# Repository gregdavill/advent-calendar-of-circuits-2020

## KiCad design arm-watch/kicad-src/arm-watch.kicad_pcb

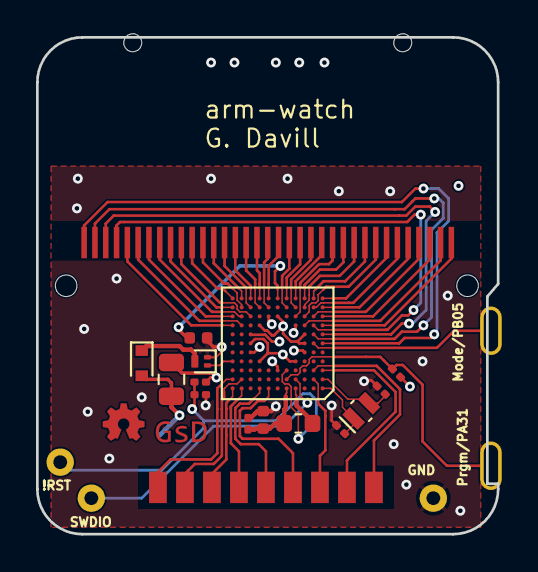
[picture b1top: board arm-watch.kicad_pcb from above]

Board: 4 copper layers, 25.6 x 27.6 mm, 17 parts (0 on the bottom side), 58 nets.

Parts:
BRD1: CA53BOARD; ca53board
C1, C2: 8pF; C_0201_0603Metric
C3, C4: 0.1uF; C_0201_0603Metric
C5: 4.7uF; C_0402_1005Metric
C6: 4.7uF; R_0402_1005Metric
D1: D_Schottky_ALT; D_SOD-523
KPD1: CA53KEYPAD; ca53keypad
L1: 10uH; L_0603_1608Metric
L2: 10uH; L_0805_2012Metric
LCD1: CA53LCD; ca53lcd
Q1: Q_NMOS_GSD; SOT-883
R1: 1k; R_0201_0603Metric
R2: 10K; R_0201_0603Metric
U1: ATSAML22N16A-CFUT; BGA-100_6.0x6.0mm_Layout11x11_P0.5mm_Ball0.3mm_Pad0.25mm_NS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
Y1: 32.768KHz; Crystal_SMD_MicroCrystal_CM9V-T1A-2Pin_1.6x1.0mm

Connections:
+3V0: BRD1.1 (VCC), L2.1, R1.1, R2.1, U1.D4 (VDDIO[5]), U1.D8 (VDDIO[5]), U1.F3 (VDDANA[2]), U1.F9 (VDDIO[5]), U1.G3 (VDDANA[2]), U1.H8 (VDDIO[5]), U1.J6 (VDDIO[5])
/BUZZER: Q1.1 (G), U1.D11 (PB20/EIC[4]/LP[46]/SC3[0]/SC5[0])
/KEY0: KPD1.1, U1.B11 (PA22/EIC[6]/LP[50]/SC0[2]/SC2[0])
/KEY1: KPD1.2, U1.B10 (PA23/EIC[7]/LP[51]/SC0[3]/SC2[1])
/KEY2: KPD1.3, U1.A11 (PA24/EIC[12]/SC2[2]/SC5[0])
/KEY3: KPD1.4, U1.A10 (PA25/EIC[13]/SC2[3]/SC5[1])
/KEY4: KPD1.5, U1.A8 (PB23/EIC[7]/SC0[3]/SC5[3])
/KEY5: KPD1.6, U1.A7 (PC27/EIC[3]/SC1[0])
/KEY6: KPD1.7, U1.B2 (PB01/EIC[1]/SC3[3]/SC5[3])
/KEY7: KPD1.8, U1.C1 (PC02/EIC[10])
/KEY8: KPD1.9, U1.C2 (PC01/EIC[9])
/LCD_COM0: LCD1.1 (COM0), U1.F1 (PB06/EIC[6]/LP[0])
/LCD_COM1: LCD1.2 (COM1), U1.G2 (PB07/EIC[7]/LP[1])
/LCD_COM2: LCD1.3 (COM2), U1.G1 (PB08/EIC[8]/LP[2]/SC3[0])
/LCD_COM3: LCD1.4 (COM3), U1.H2 (PB09/EIC[9]/LP[3]/SC3[1])
/LCD_SEG0: LCD1.5 (SEG01), U1.H11 (PC18/EIC[10]/LP[38])
/LCD_SEG1: LCD1.6 (SEG02), U1.H10 (PC17/EIC[9]/LP[37])
/LCD_SEG2: LCD1.7 (SEG03), U1.J11 (PC16/EIC[8]/LP[36])
/LCD_SEG3: LCD1.8 (SEG04), U1.J10 (PA19/EIC[3]/LP[35]/SC1[3]/SC2[3])
/LCD_SEG4: LCD1.9 (SEG04), U1.K11 (PA17/EIC[1]/LP[33]/SC1[1]/SC2[1])
/LCD_SEG5: LCD1.10 (SEG05), U1.J9 (PA16/EIC[0]/LP[32]/SC1[0]/SC2[0])
/LCD_SEG6: LCD1.11 (SEG06), U1.L11 (PA15/EIC[15]/LP[31]/SC4[3]/SC3[3])
/LCD_SEG7: LCD1.12 (SEG07), U1.K10 (PA14/EIC[14]/LP[30]/SC4[2]/SC3[2])
/LCD_SEG8: LCD1.13 (SEG08), U1.L10 (PA13/EIC[13]/LP[29]/SC4[1]/SC3[1])
/LCD_SEG9: LCD1.14 (SEG09), U1.K9 (PA12/EIC[12]/LP[28]/SC4[0]/SC3[0])
/LCD_SEG10: LCD1.15 (SEG10), U1.L9 (PC15/EIC[7]/LP[27])
/LCD_SEG11: LCD1.16 (SEG11), U1.K8 (PB14/EIC[14]/LP[24]/SC3[2])
/LCD_SEG12: LCD1.17 (SEG12), U1.L8 (PB15/EIC[15]/LP[25]/SC3[3])
/LCD_SEG13: LCD1.18 (SEG13), U1.K7 (PB12/EIC[12]/LP[22]/SC3[0])
/LCD_SEG14: LCD1.19 (SEG14), U1.L7 (PB13/EIC[13]/LP[23]/SC3[1])
/LCD_SEG15: LCD1.20 (SEG15), U1.K5 (PC12/EIC[4]/LP[19]/SC1[0])
/LCD_SEG16: LCD1.21 (SEG16), U1.L5 (PC13/EIC[5]/LP[20]/SC1[1])
/LCD_SEG17: LCD1.22 (SEG17), U1.K4 (PC10/EIC[2]/LP[17]/SC1[2])
/LCD_SEG18: LCD1.23 (SEG18), U1.L4 (PC11/EIC[3]/LP[18]/SC1[3])
/LCD_SEG19: LCD1.24 (SEG19), U1.J4 (PA10/EIC[10]/LP[13]/SC0[2]/SC4[2])
/LCD_SEG20: LCD1.25 (SEG20), U1.L3 (PC08/EIC[0]/LP[15])
/LCD_SEG21: LCD1.26 (SEG21), U1.K3 (PA11/EIC[11]/LP[14]/SC0[3]/SC4[3])
/LCD_SEG22: LCD1.27 (SEG22), U1.L2 (PA09/EIC[9]/LP[12]/SC0[1]/SC4[1])
/LCD_SEG23: LCD1.28 (SEG23), U1.J3 (PC07/EIC[15]/LP[10])
/LCD_SEG24: LCD1.29 (SEG24), U1.L1 (PA08/NMI/LP[11]/SC0[0]/SC4[0])
/LCD_SEG25: LCD1.30 (SEG25), U1.K2 (PC06/EIC[14]/LP[9])
/LCD_SEG26: LCD1.31 (SEG26), U1.K1 (PC05/EIC[13]/LP[8])
/LCD_SEG27: LCD1.32 (SEG27), U1.J2 (PA07/EIC[7]/LP[7]/SC0[3])
/LCD_SEG28: LCD1.33 (SEG28), U1.J1 (PA06/EIC[6]/LP[6]/SC0[2])
/LCD_SEG29: LCD1.34 (SEG29), U1.H3 (PA05/EIC[5]/LP[5]/SC0[1])
/LCD_SEG30: LCD1.35 (SEG30), U1.H1 (PA04/EIC[4]/LP[4]/SC0[0])
/MODE: BRD1.3 (MODE), U1.F2 (PB05/EIC[5])
/RST_N: BRD1.6 (!RST), C4.1, R2.2, U1.C5 (RESET_N)
/SWCLK: BRD1.4 (PRGM), R1.2, U1.B5 (PA30/EIC[10]/SC1[2]/SWCLK)
/SWDIO: BRD1.5 (TST), U1.B4 (PA31/EIC[11]/SC1[3]/SWDIO)
GND: BRD1.2 (GND), BRD1.7 (GND), C1.2, C2.2, C3.2, C4.2, C5.2, C6.2, Q1.2 (S), U1.C6 (GNDIO[5]), U1.E3 (GNDANA[2]), U1.E9 (GNDIO[5]), U1.G9 (GNDIO[5]), U1.H4 (GNDANA[2]), U1.J7 (GNDIO[5])
unnamed: BRD1.8 (BUZZ), D1.2 (A), L2.2
unnamed: C1.1, U1.B1 (PA01/EIC[1]/SC1[1]), Y1.2
unnamed: C2.1, U1.A1 (PA00/EIC[0]/SC1[0]), Y1.1
unnamed: C3.1, C5.1, L1.2, U1.A5 (VDDCORE)
unnamed: D1.1 (K), Q1.3 (D)
unnamed: L1.1, U1.A4 (VSW)
unnamed: C6.1, U1.L6 (VLCD)

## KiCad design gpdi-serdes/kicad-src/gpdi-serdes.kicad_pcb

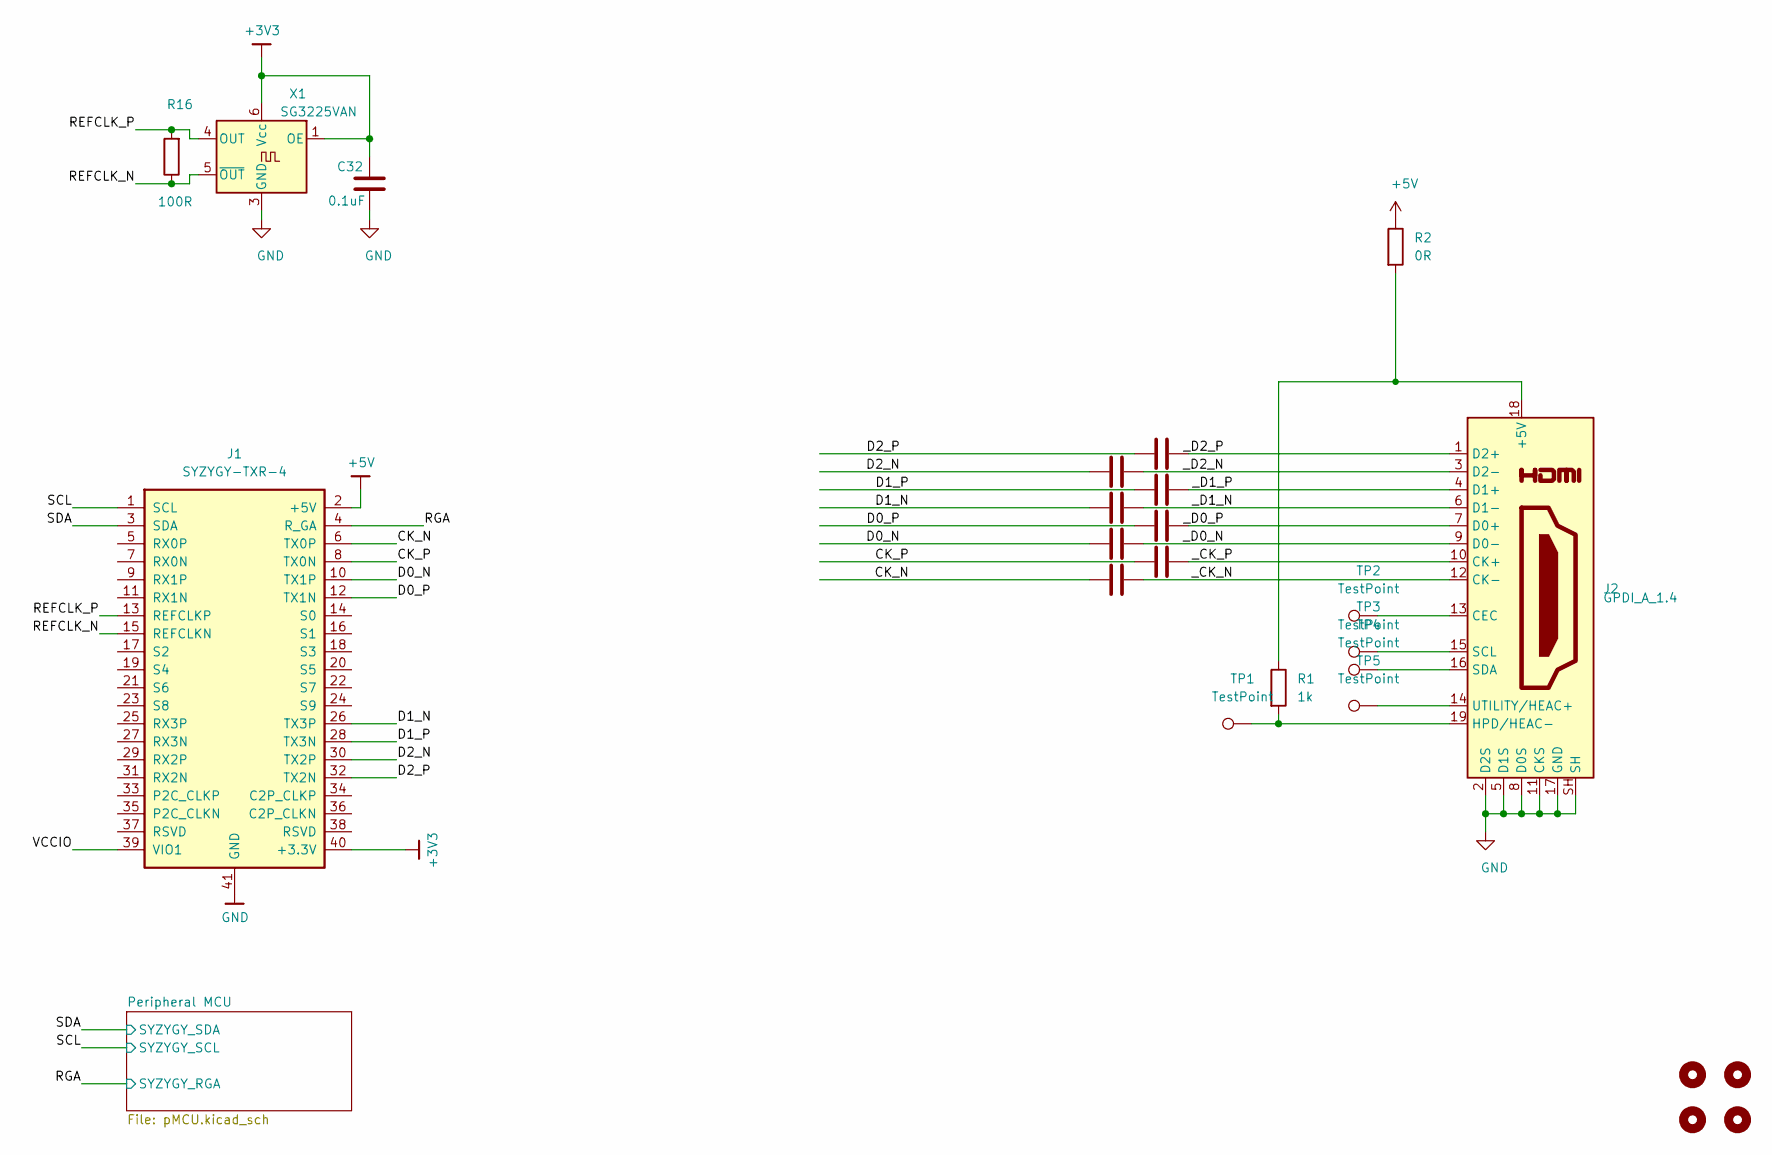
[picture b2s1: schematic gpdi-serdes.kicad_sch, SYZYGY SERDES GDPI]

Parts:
C1, C2, C3, C4, C5, C6, C7, C8: 0.1u; C_0402_1005Metric
C32: 0.1uF; C_0402_1005Metric
H1, H2, H3, H4: MountingHole; MountingHole_3.2mm_M3
J1: SYZYGY-TXR-4; SYZYGY-TXR-POD
J2: GPDI_A_1.4; HDMI-10029449-111RLF
R1: 1k; R_0402_1005Metric
R2: 0R; R_0402_1005Metric
R16: 100R; R_0402_1005Metric
TP1, TP2, TP3, TP4, TP5: TestPoint; TestPoint_THTPad_D1.5mm_Drill0.7mm
X1: SG3225VAN; Oscillator_SMD_Silicon_Labs_LGA-6_2.5x3.2mm_P1.25mm

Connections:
+3V3: C32.1, J1.40 (+3.3V), X1.1 (OE), X1.6 (Vcc); also elsewhere on the board
+5V: J1.2 (+5V), R2.1
/CK_N: C4.1, J1.6 (TX0P)
/CK_P: C8.1, J1.8 (TX0N)
/D0_N: C3.1, J1.10 (TX1P)
/D0_P: C7.1, J1.12 (TX1N)
/D1_N: C2.1, J1.26 (TX3P)
/D1_P: C6.1, J1.28 (TX3N)
/D2_N: C1.1, J1.30 (TX2P)
/D2_P: C5.1, J1.32 (TX2N)
/REFCLK_N: J1.15 (REFCLKN), R16.1, X1.5 (~OUT)
/REFCLK_P: J1.13 (REFCLKP), R16.2, X1.4 (OUT)
/RGA: J1.4 (R_GA); also elsewhere on the board
/SCL: J1.1 (SCL); also elsewhere on the board
/SDA: J1.3 (SDA); also elsewhere on the board
/VCCIO: J1.39 (VIO1)
/_CK_N: C4.2, J2.12 (CK-)
/_CK_P: C8.2, J2.10 (CK+)
/_D0_N: C3.2, J2.9 (D0-)
/_D0_P: C7.2, J2.7 (D0+)
/_D1_N: C2.2, J2.6 (D1-)
/_D1_P: C6.2, J2.4 (D1+)
/_D2_N: C1.2, J2.3 (D2-)
/_D2_P: C5.2, J2.1 (D2+)
GND: C32.2, J1.41 (GND), J2.2 (D2S), J2.5 (D1S), J2.8 (D0S), J2.11 (CKS), J2.17 (GND), J2.SH, X1.3 (GND); also elsewhere on the board
unnamed: J2.13 (CEC), TP2.1
unnamed: J2.14 (UTILITY/HEAC+), TP5.1
unnamed: J2.15 (SCL), TP3.1
unnamed: J2.16 (SDA), TP4.1
unnamed: J2.18 (+5V), R1.1, R2.2
unnamed: J2.19 (HPD/HEAC-), R1.2, TP1.1

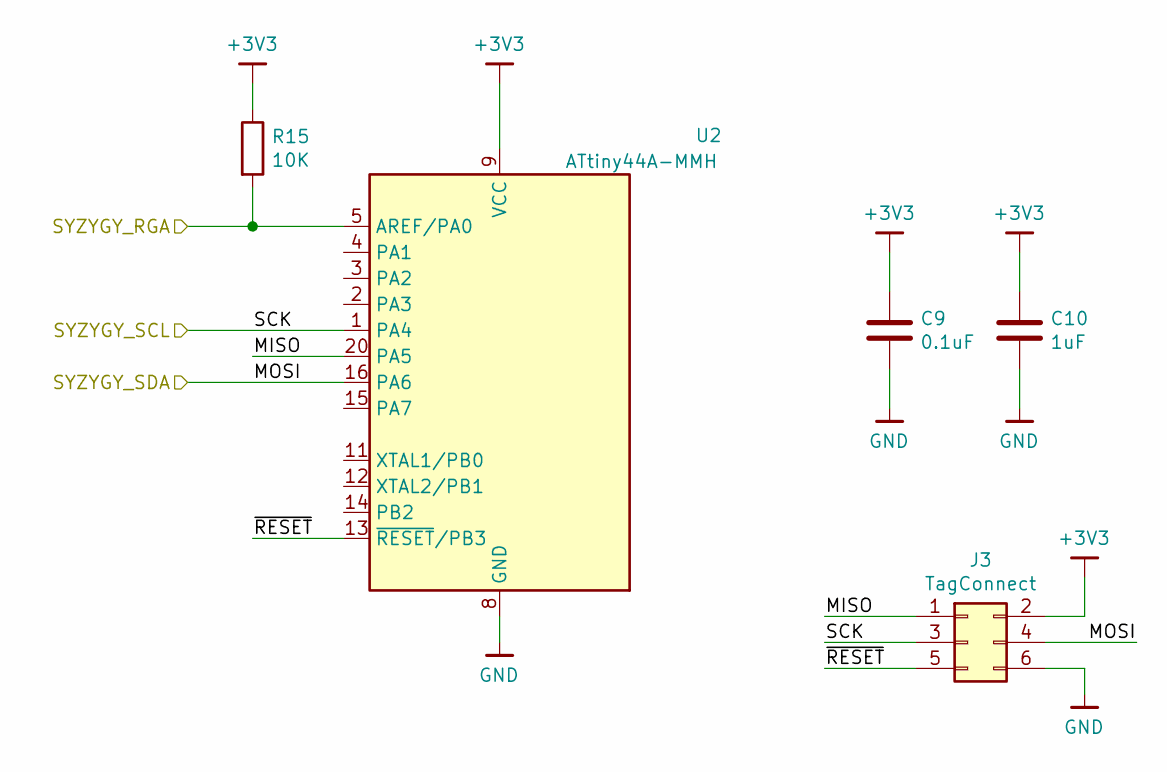
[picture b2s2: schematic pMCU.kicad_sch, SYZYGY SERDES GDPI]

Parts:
C9: 0.1uF; C_0402_1005Metric
C10: 1uF; C_0402_1005Metric
J3: TagConnect; TC2030-NL_SMALL
R15: 10K; R_0402_1005Metric
U2: ATtiny44A-MMH; QFN-20-1EP_3x3mm_P0.45mm_EP1.6x1.6mm

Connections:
+3V3: C9.1, C10.1, J3.2, R15.1, U2.9 (VCC); also elsewhere on the board
/Peripheral MCU/MISO: J3.1, U2.20 (PA5)
/Peripheral MCU/~RESET: J3.5, U2.13 (~RESET~/PB3)
/RGA: R15.2, U2.5 (AREF/PA0); also elsewhere on the board
/SCL: J3.3, U2.1 (PA4); also elsewhere on the board
/SDA: J3.4, U2.16 (PA6); also elsewhere on the board
GND: C9.2, C10.2, J3.6, U2.8 (GND), U2.21 (GND); also elsewhere on the board
no_connect_65: U2.10 (NC)
no_connect_66: U2.17 (NC)
no_connect_67: U2.18 (NC)
no_connect_68: U2.19 (NC)
no_connect_69: U2.6 (NC)
no_connect_70: U2.7 (NC)

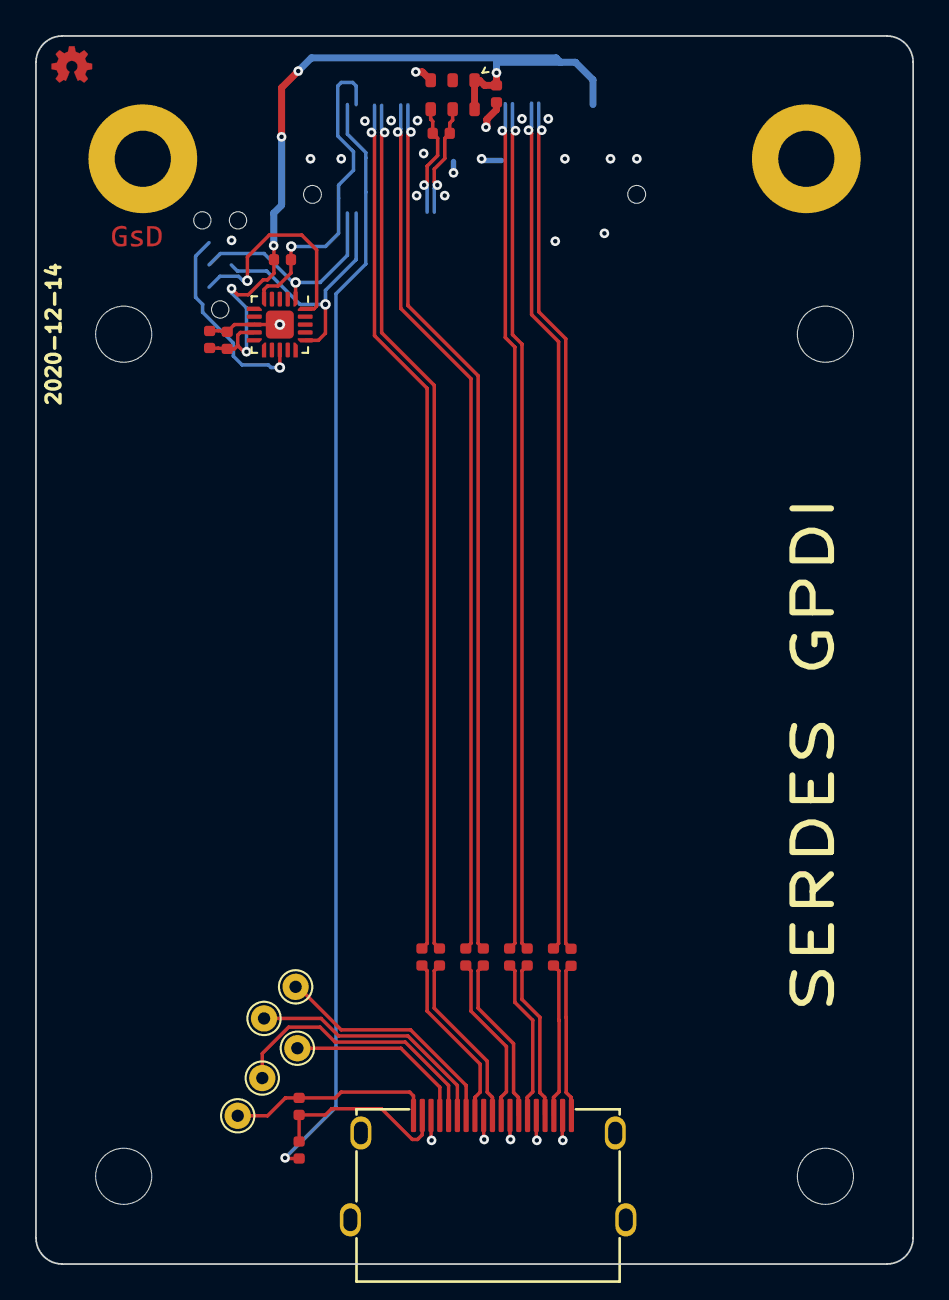
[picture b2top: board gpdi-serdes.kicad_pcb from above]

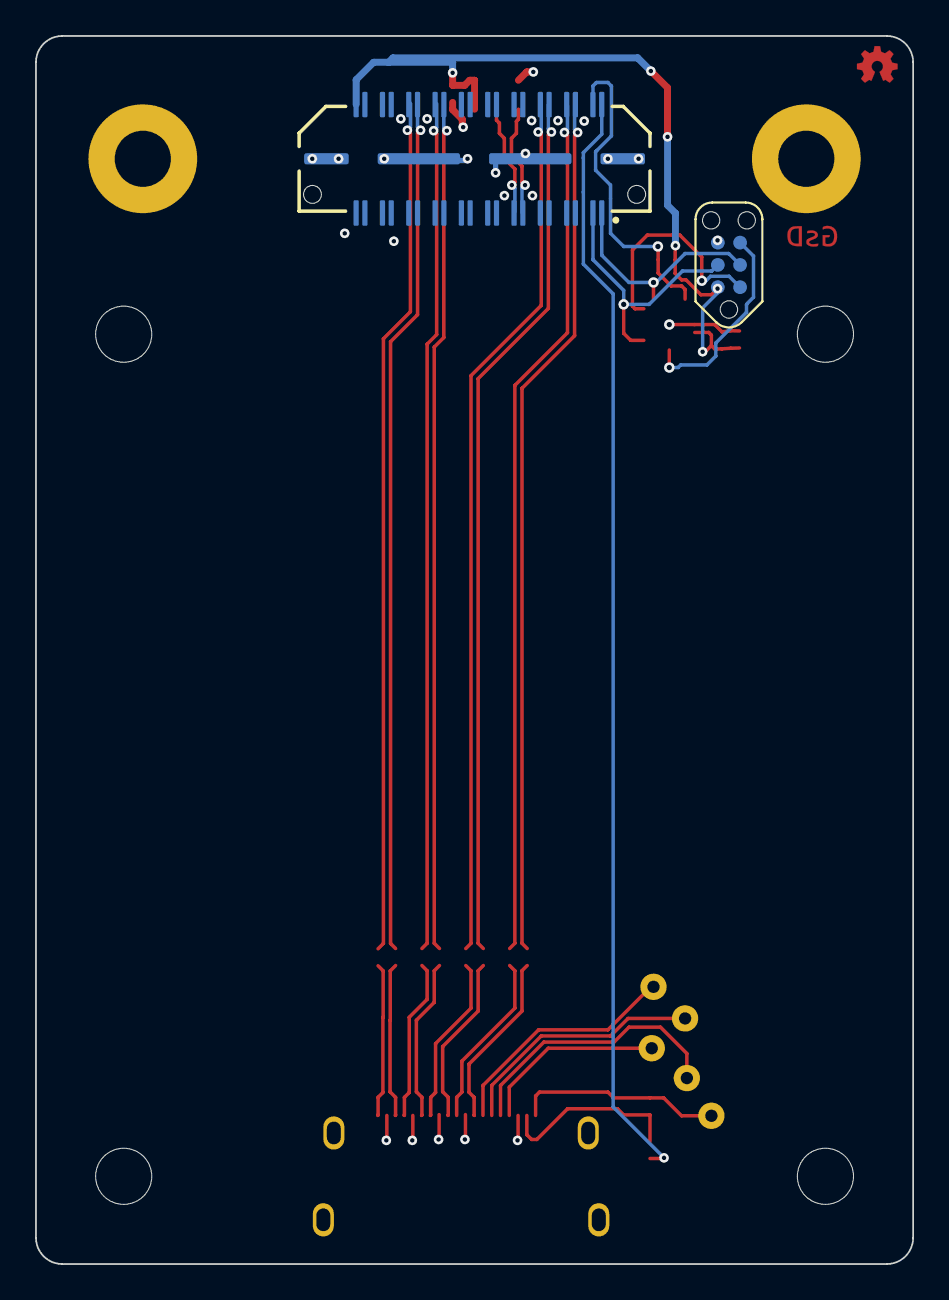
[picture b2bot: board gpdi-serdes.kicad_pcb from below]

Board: 4 copper layers, 50.0 x 70.0 mm, 29 parts (2 on the bottom side), 32 nets.

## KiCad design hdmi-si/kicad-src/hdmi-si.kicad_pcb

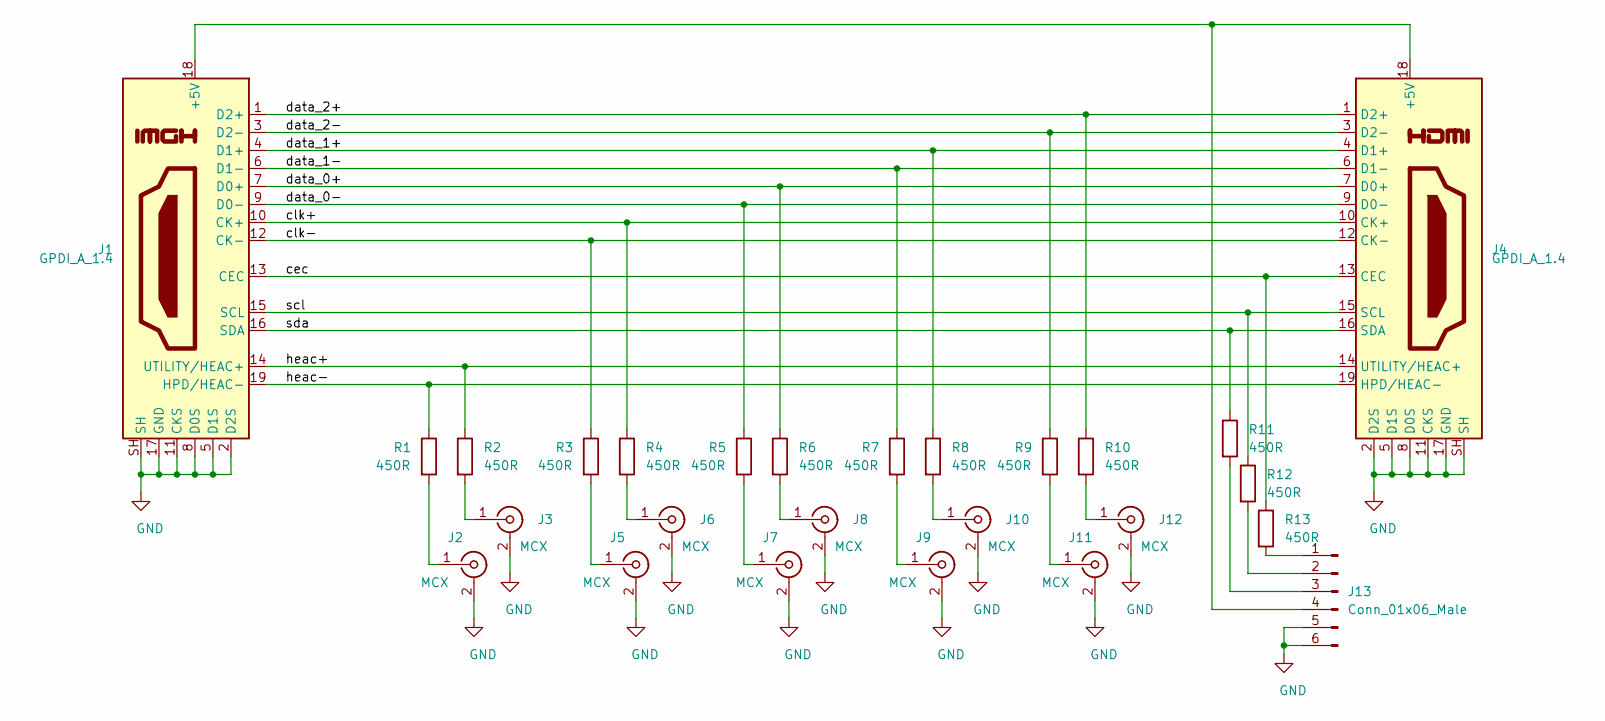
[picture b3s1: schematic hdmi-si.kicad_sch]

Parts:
J1, J4: GPDI_A_1.4; HDMI-10029449-111RLF
J2, J3, J5, J6, J7, J8, J9, J10, J11, J12: MCX; MMCX_Molex_73415-1471_Vertical
J13: Conn_01x06_Male; PinHeader_1x06_P2.54mm_Vertical
R1, R2, R3, R4, R5, R6, R7, R8, R9, R10, R11, R12, R13: 450R; R_0402_1005Metric

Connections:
/cec: J1.13 (CEC), J4.13 (CEC), R13.1
/clk+: J1.10 (CK+), J4.10 (CK+), R4.1
/clk-: J1.12 (CK-), J4.12 (CK-), R3.1
/data_0+: J1.7 (D0+), J4.7 (D0+), R6.1
/data_0-: J1.9 (D0-), J4.9 (D0-), R5.1
/data_1+: J1.4 (D1+), J4.4 (D1+), R8.1
/data_1-: J1.6 (D1-), J4.6 (D1-), R7.1
/data_2+: J1.1 (D2+), J4.1 (D2+), R10.1
/data_2-: J1.3 (D2-), J4.3 (D2-), R9.1
/heac+: J1.14 (UTILITY/HEAC+), J4.14 (UTILITY/HEAC+), R2.1
/heac-: J1.19 (HPD/HEAC-), J4.19 (HPD/HEAC-), R1.1
/scl: J1.15 (SCL), J4.15 (SCL), R12.1
/sda: J1.16 (SDA), J4.16 (SDA), R11.1
GND: J1.2 (D2S), J1.5 (D1S), J1.8 (D0S), J1.11 (CKS), J1.17 (GND), J1.SH, J2.2 (Ext), J3.2 (Ext), J4.2 (D2S), J4.5 (D1S), J4.8 (D0S), J4.11 (CKS), J4.17 (GND), J4.SH, J5.2 (Ext), J6.2 (Ext), J7.2 (Ext), J8.2 (Ext), J9.2 (Ext), J10.2 (Ext), J11.2 (Ext), J12.2 (Ext), J13.5, J13.6
unnamed: J1.18 (+5V), J4.18 (+5V), J13.4
unnamed: J2.1 (In), R1.2
unnamed: J3.1 (In), R2.2
unnamed: J5.1 (In), R3.2
unnamed: J6.1 (In), R4.2
unnamed: J7.1 (In), R5.2
unnamed: J8.1 (In), R6.2
unnamed: J9.1 (In), R7.2
unnamed: J10.1 (In), R8.2
unnamed: J11.1 (In), R9.2
unnamed: J12.1 (In), R10.2
unnamed: J13.1, R13.2
unnamed: J13.2, R12.2
unnamed: J13.3, R11.2

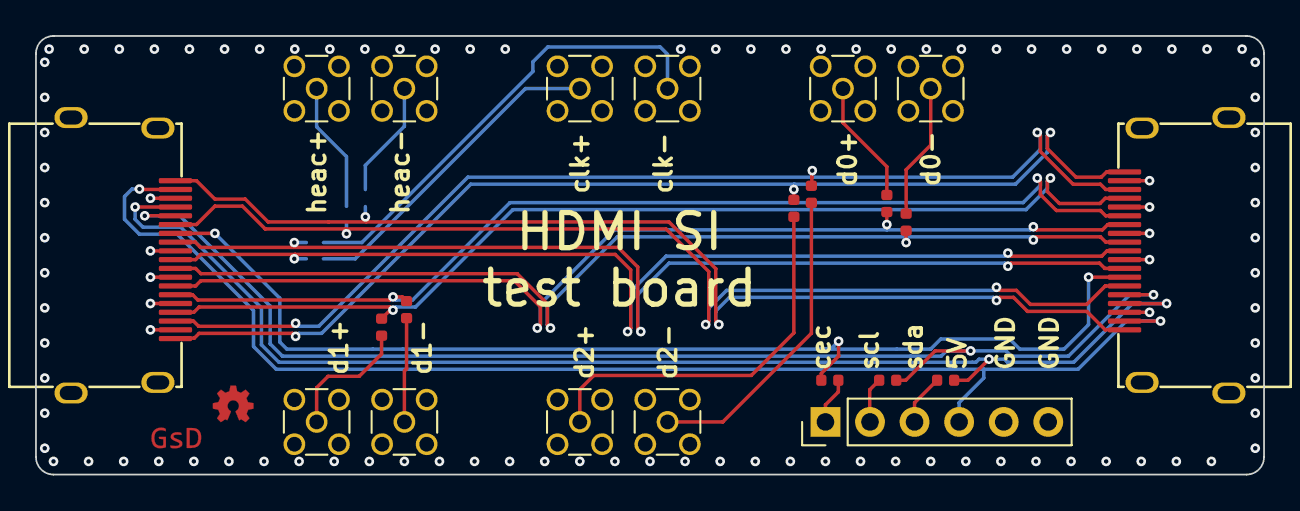
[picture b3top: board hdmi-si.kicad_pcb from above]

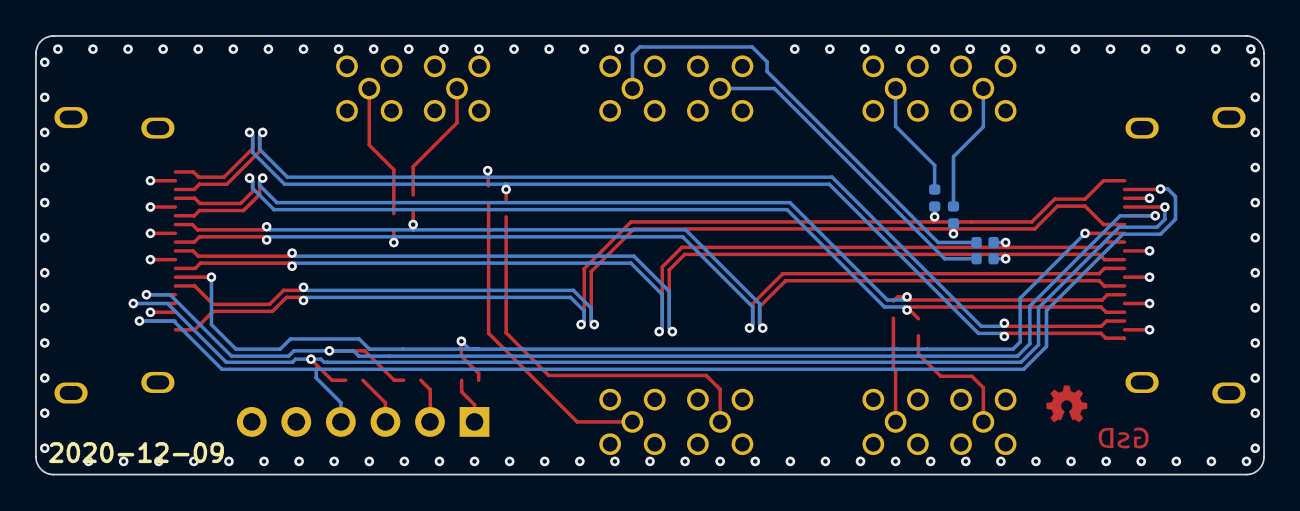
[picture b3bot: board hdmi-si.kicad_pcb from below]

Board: 4 copper layers, 70.0 x 25.0 mm, 26 parts (4 on the bottom side), 28 nets.

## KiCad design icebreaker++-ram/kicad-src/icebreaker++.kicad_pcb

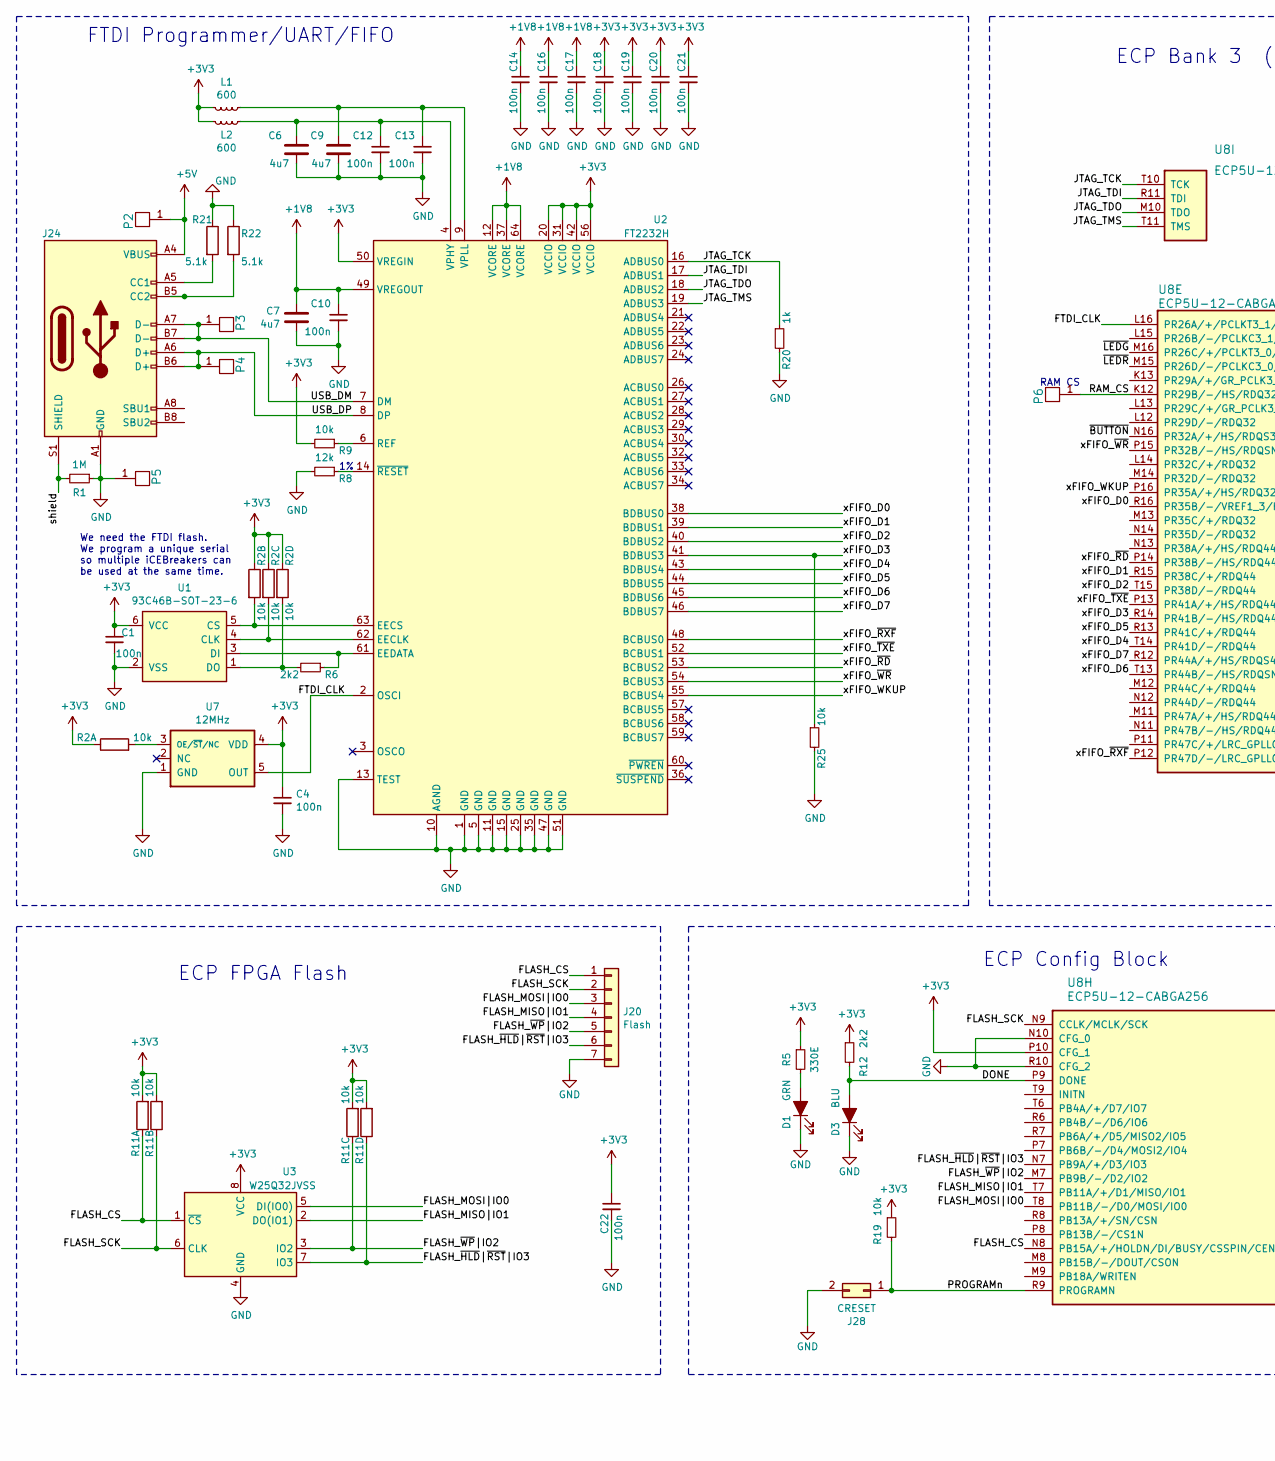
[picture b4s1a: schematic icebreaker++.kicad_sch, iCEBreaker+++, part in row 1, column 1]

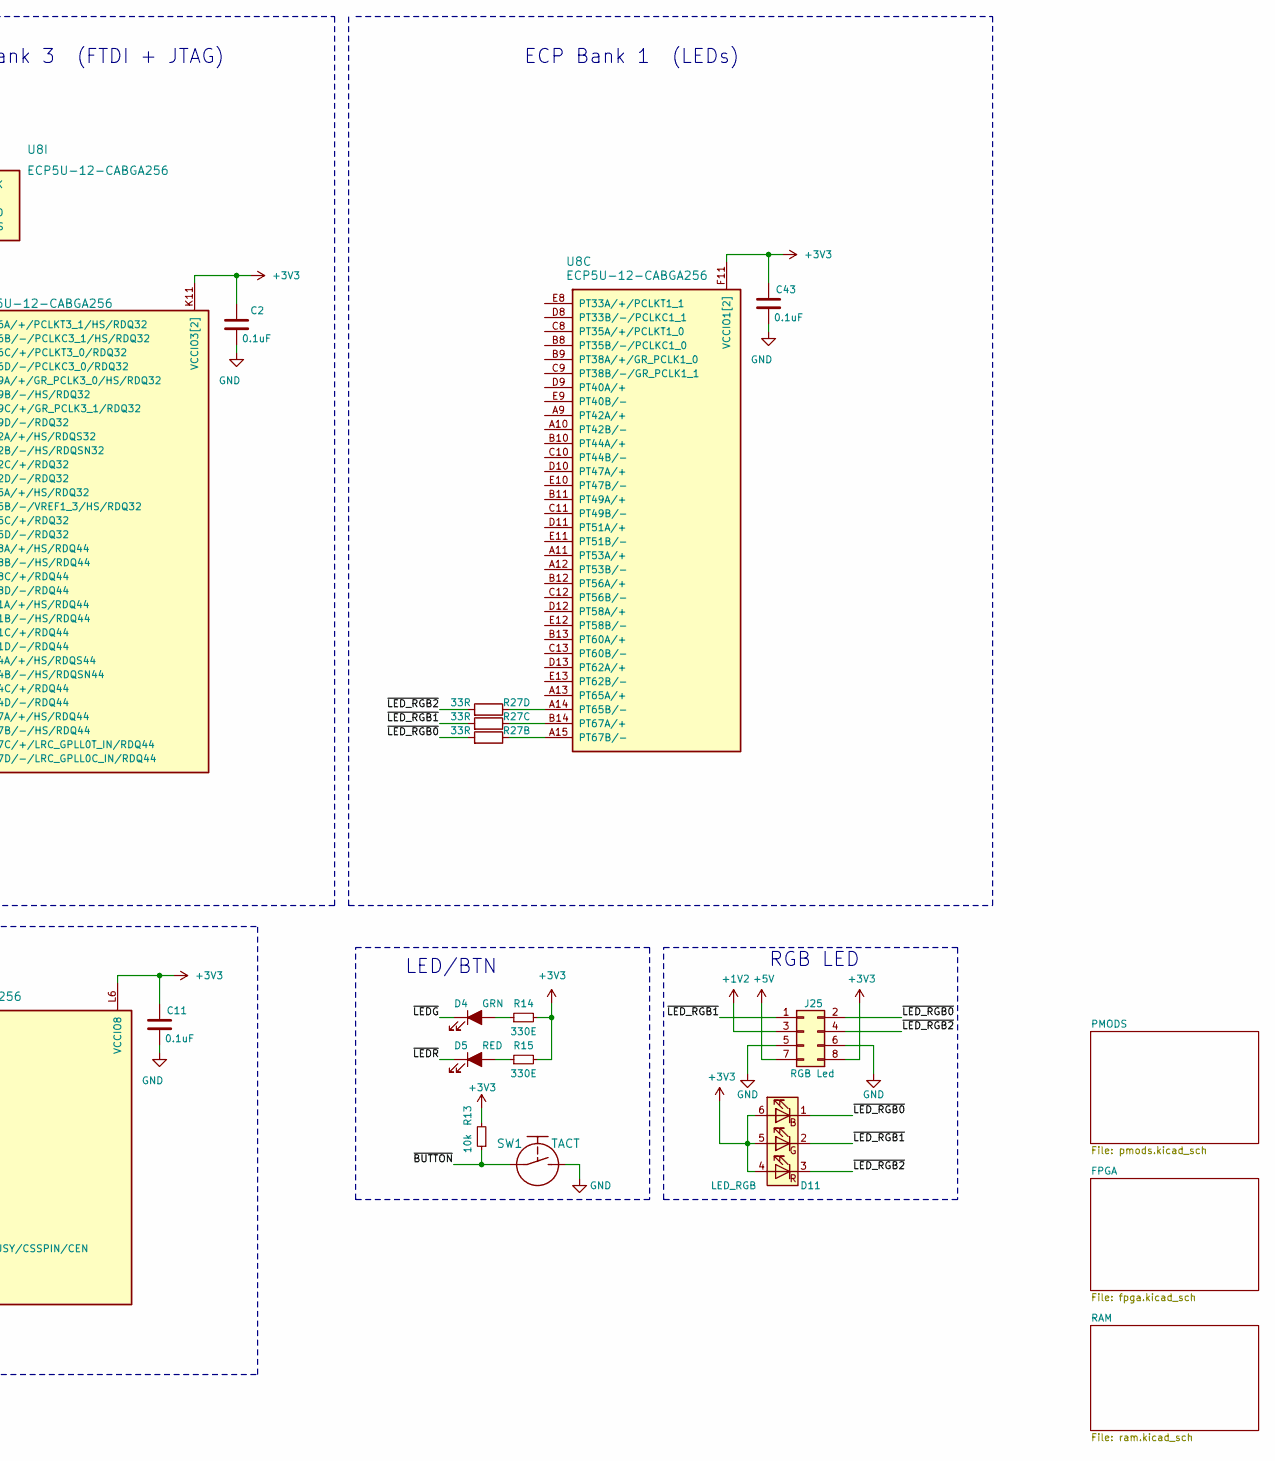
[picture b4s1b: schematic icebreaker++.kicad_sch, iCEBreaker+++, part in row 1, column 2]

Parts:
C1, C4, C10, C12, C13, C14, C16, C17, C18, C19, C20, C21, C22: 100n; C_0402_1005Metric
C2, C11, C43: 0.1uF; C_0402_1005Metric
C6, C7, C9: 4u7; C_0603_1608Metric
D1, D4: GRN; LED_0603_1608Metric
D3: BLU; LED_0603_1608Metric
D5: RED; LED_0603_1608Metric
D11: LED_RGB; LED_Cree_PLCC6_3.4x3.4mm
J20: Flash; PinHeader_1x07_P2.54mm_Vertical
J24: USB_C_Receptacle_USB2.0; USB_C_Receptacle_HRO_TYPE-C-31-M-12
J25: RGB Led; PinHeader_2x04_P2.54mm_Vertical
J28: CRESET; PinHeader_2x01_P2.54mm_Vertical
L1, L2: 600; L_0402_1005Metric
P2, P3, P4, P5: UP; PAD_SMD_1x2.65
P6: RAM_CS; PAD_SMD_1x1.5
R1: 1M; R_0402_1005Metric
R2, R11: 10k; R_Array_Convex_4x0402
R5, R14, R15: 330E; R_0402_1005Metric
R6, R12: 2k2; R_0402_1005Metric
R8: 12k; R_0402_1005Metric
R9, R13, R19, R25: 10k; R_0402_1005Metric
R20: 1k; R_0402_1005Metric
R21, R22: 5.1k; R_0402_1005Metric
R27: 33R; R_Array_Convex_4x0402
SW1: TACT; SW_SPST_PTS810
U1: 93C46B-SOT-23-6; SOT-23-6
U2: FT2232H; QFN-64-1EP_9x9mm_P0.5mm_EP4.35x4.35mm
U3: W25Q32JVSS; SOIC-8_5.23x5.23mm_P1.27mm
U7: 12MHz; SOT-23-5
U8: ECP5U-12-CABGA256; BGA-256_14.0x14.0mm_Layout16x16_P0.8mm_Ball0.45mm_Pad0.32mm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

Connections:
+1V2: J25.3
+1V8: C7.1, C10.1, C14.1, C16.1, C17.1, U2.12 (VCORE), U2.37 (VCORE), U2.49 (VREGOUT), U2.64 (VCORE); also elsewhere on the board
+3V3: C1.1, C2.1, C4.1, C11.1, C18.1, C19.1, C20.1, C21.1, C22.1, C43.1, D11.4 (BA), D11.5 (GA), D11.6 (RA), J25.8, L1.1, L2.1, R2.5, R2.6, R2.7, R2.8, R5.1, R9.2, R11.1, R11.2, R11.3, R11.4, R12.1, R13.2, R14.2, R15.2, R19.1, U1.6 (VCC), U2.20 (VCCIO), U2.31 (VCCIO), U2.42 (VCCIO), U2.50 (VREGIN), U2.56 (VCCIO), U3.8 (VCC), U7.4 (VDD), U8.F10 (VCCIO1[2]), U8.F11 (VCCIO1[2]), U8.K11 (VCCIO3[2]), U8.L6 (VCCIO8), U8.L11 (VCCIO3[2]), U8.P10 (CFG_1); also elsewhere on the board
+5V: J24.A4 (VBUS), J24.A9 (VBUS), J24.B4 (VBUS), J24.B9 (VBUS), J25.7, P2.1 (PAD); also elsewhere on the board
/DONE: D3.2 (A), R12.2, U8.P9 (DONE)
/FLASH_CS: J20.1, R11.8, U3.1 (~CS), U8.N8 (PB15A/+/HOLDN/DI/BUSY/CSSPIN/CEN)
/FLASH_MISO|IO1: J20.4, U3.2 (DO(IO1)), U8.T7 (PB11A/+/D1/MISO/IO1)
/FLASH_MOSI|IO0: J20.3, U3.5 (DI(IO0)), U8.T8 (PB11B/-/D0/MOSI/IO0)
/FLASH_SCK: J20.2, R11.7, U3.6 (CLK), U8.N9 (CCLK/MCLK/SCK)
/FLASH_~HLD~|~RST~|IO3: J20.6, R11.5, U3.7 (IO3), U8.N7 (PB9A/+/D3/IO3)
/FLASH_~WP~|IO2: J20.5, R11.6, U3.3 (IO2), U8.M7 (PB9B/-/D2/IO2)
/FTDI_CLK: U2.2 (OSCI), U7.5 (OUT), U8.L16 (PR26A/+/PCLKT3_1/HS/RDQ32)
/JTAG_TCK: R20.1, U2.16 (ADBUS0), U8.T10 (TCK)
/JTAG_TDI: U2.17 (ADBUS1), U8.R11 (TDI)
/JTAG_TDO: U2.18 (ADBUS2), U8.M10 (TDO)
/JTAG_TMS: U2.19 (ADBUS3), U8.T11 (TMS)
/PROGRAMn: J28.1, R19.2, U8.R9 (PROGRAMN)
/RAM_CS: P6.1 (PAD), U8.K12 (PR29B/-/HS/RDQ32)
/USB_DM: J24.A7 (D-), J24.B7 (D-), P3.1 (PAD), U2.7 (DM)
/USB_DP: J24.A6 (D+), J24.B6 (D+), P4.1 (PAD), U2.8 (DP)
/shield: J24.S1 (SHIELD), R1.2
/xFIFO_D0: U2.38 (BDBUS0), U8.R16 (PR35B/-/VREF1_3/HS/RDQ32)
/xFIFO_D1: U2.39 (BDBUS1), U8.R15 (PR38C/+/RDQ44)
/xFIFO_D2: U2.40 (BDBUS2), U8.T15 (PR38D/-/RDQ44)
/xFIFO_D3: R25.1, U2.41 (BDBUS3), U8.R14 (PR41B/-/HS/RDQ44)
/xFIFO_D4: U2.43 (BDBUS4), U8.T14 (PR41D/-/RDQ44)
/xFIFO_D5: U2.44 (BDBUS5), U8.R13 (PR41C/+/RDQ44)
/xFIFO_D6: U2.45 (BDBUS6), U8.T13 (PR44B/-/HS/RDQSN44)
/xFIFO_D7: U2.46 (BDBUS7), U8.R12 (PR44A/+/HS/RDQS44)
/xFIFO_WKUP: U2.55 (BCBUS4), U8.P16 (PR35A/+/HS/RDQ32)
/xFIFO_~RD: U2.53 (BCBUS2), U8.P14 (PR38B/-/HS/RDQ44)
/xFIFO_~RXF: U2.48 (BCBUS0), U8.P12 (PR47D/-/LRC_GPLL0C_IN/RDQ44)
/xFIFO_~TXE: U2.52 (BCBUS1), U8.P13 (PR41A/+/HS/RDQ44)
/xFIFO_~WR: U2.54 (BCBUS3), U8.P15 (PR32B/-/HS/RDQSN32)
/~BUTTON: R13.1, SW1.1, U8.N16 (PR32A/+/HS/RDQS32)
/~LEDG: D4.1 (K), U8.M16 (PR26C/+/PCLKT3_0/RDQ32)
/~LEDR: D5.1 (K), U8.M15 (PR26D/-/PCLKC3_0/RDQ32)
/~LED_RGB0: D11.1 (RK), J25.2, R27.2
/~LED_RGB1: D11.2 (GK), J25.1, R27.3
/~LED_RGB2: D11.3 (BK), J25.4, R27.4
GND: C1.2, C2.2, C4.2, C6.2, C7.2, C9.2, C10.2, C11.2, C12.2, C13.2, C14.2, C16.2, C17.2, C18.2, C19.2, C20.2, C21.2, C22.2, C43.2, D1.1 (K), D3.1 (K), J20.7, J24.A1 (GND), J24.A12 (GND), J24.B1 (GND), J24.B12 (GND), J25.5, J25.6, J28.2, P5.1 (PAD), R1.1, R8.2, R20.2, R21.1, R22.1, R25.2, SW1.2, U1.2 (VSS), U2.1 (GND), U2.5 (GND), U2.10 (AGND), U2.11 (GND), U2.13 (TEST), U2.15 (GND), U2.25 (GND), U2.35 (GND), U2.47 (GND), U2.51 (GND), U3.4 (GND), U7.1 (GND), U8.N10 (CFG_0), U8.R10 (CFG_2); also elsewhere on the board
unnamed: C6.1, C12.1, L2.2, U2.4 (VPHY)
unnamed: C9.1, C13.1, L1.2, U2.9 (VPLL)
unnamed: D1.2 (A), R5.2
unnamed: D4.2 (A), R14.1
unnamed: D5.2 (A), R15.1
unnamed: J24.A5 (CC1), R21.2
unnamed: J24.B5 (CC2), R22.2
unnamed: R2.1, U7.3 (OE/~ST~/NC)
unnamed: R2.2, U1.5 (CS), U2.63 (EECS)
unnamed: R2.3, U1.4 (CLK), U2.62 (EECLK)
unnamed: R2.4, R6.2, U1.1 (DO)
unnamed: R6.1, U1.3 (DI), U2.61 (EEDATA)
unnamed: R8.1, U2.14 (~RESET)
unnamed: R9.1, U2.6 (REF)
unnamed: R27.5, U8.A14 (PT65B/-)
unnamed: R27.7, U8.A15 (PT67B/-)
unnamed: R27.6, U8.B14 (PT67A/+)
no_connect_265: U2.21 (ADBUS4)
no_connect_266: U2.22 (ADBUS5)
no_connect_267: U2.23 (ADBUS6)
no_connect_268: U2.24 (ADBUS7)
no_connect_269: U2.26 (ACBUS0)
no_connect_270: U2.27 (ACBUS1)
no_connect_271: U2.28 (ACBUS2)
no_connect_272: U2.29 (ACBUS3)
no_connect_273: U2.3 (OSCO)
no_connect_274: U2.30 (ACBUS4)
no_connect_275: U2.32 (ACBUS5)
no_connect_276: U2.33 (ACBUS6)
no_connect_277: U2.34 (ACBUS7)
no_connect_278: U2.36 (~SUSPEND)
no_connect_279: U2.57 (BCBUS5)
no_connect_280: U2.58 (BCBUS6)
no_connect_281: U2.59 (BCBUS7)
no_connect_282: U2.60 (~PWREN)
no_connect_286: U7.2 (NC)

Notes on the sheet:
We need the FTDI flash. We program a unique serial so multiple iCEBreakers can be used at the same time.
FTDI Programmer/UART/FIFO
ECP FPGA Flash
ECP Config Block
RAM CS
ECP Bank 3 (FTDI + JTAG)
LED/BTN
ECP Bank 1 (LEDs)
RGB LED

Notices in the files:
icebreaker++-ram/kicad-src/icebreaker++.kicad_pcb:
License: CC-BY-SA 4.0
GsD (C) 2020
CC-BY-SA 4.0
(C) 2020
icebreaker++-ram/kicad-src/icebreaker++.kicad_sch:
License: CC-BY-SA V4.0
